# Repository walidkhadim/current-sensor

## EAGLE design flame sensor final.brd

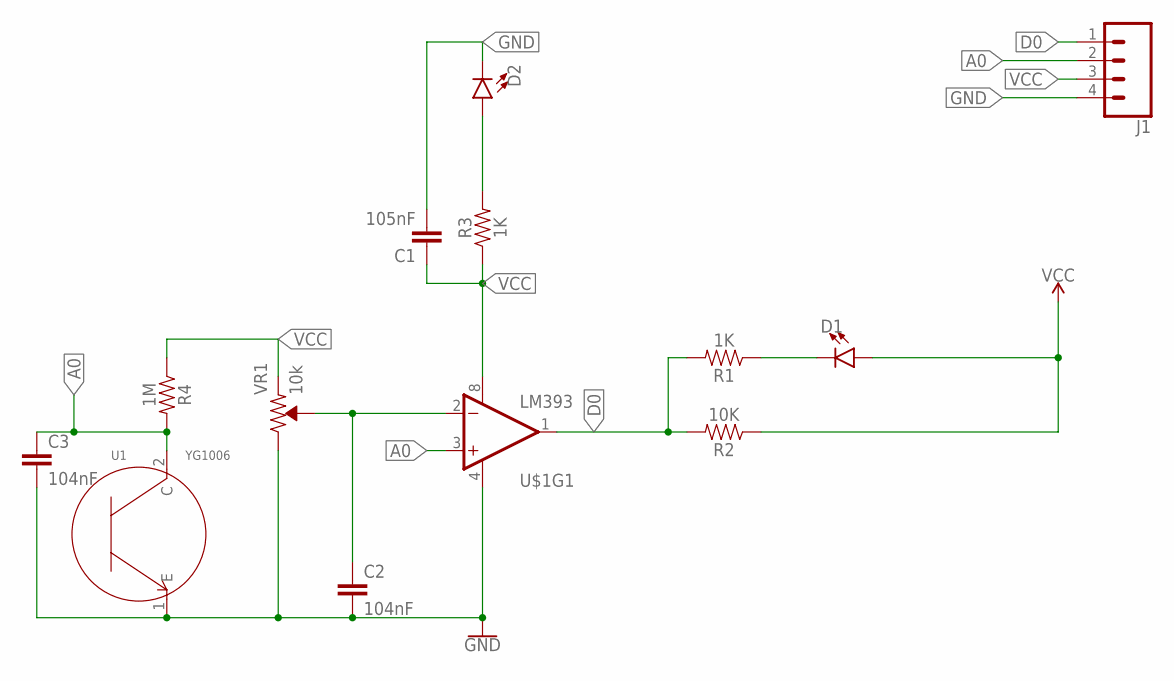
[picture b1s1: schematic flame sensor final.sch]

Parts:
C1: 105nF; 1206
C2, C3: 104nF; 1206
D1, D2: LED1206; LED-1206
J1: CONN_04; 1X04
R1, R3: 1K; 0603
R2: 10K; 0603
R4: 1M; 0603
U1: YG1006; 2P-2.54-5MM
U$1: LM393; SO08
VR1: 10k; TRIMPOT-SMD-5MM

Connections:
A0: C3.1, J1.2, R4.2, U1.2 (C), U$1.3 (+IN)
D0: J1.1, R1.2, R2.2, U$1.1 (OUT)
GND: C1.2, C2.2, C3.2, D2.C, J1.4, U1.1 (E), U$1.4 (V-), VR1.C (CW)
unnamed: D1.C, R1.1
unnamed: C2.1, U$1.2 (-IN), VR1.B (WIPER)
unnamed: D2.A, R3.2
VCC: C1.1, D1.A, J1.3, R2.1, R3.1, R4.1, U$1.8 (V+), VR1.A (CCW)

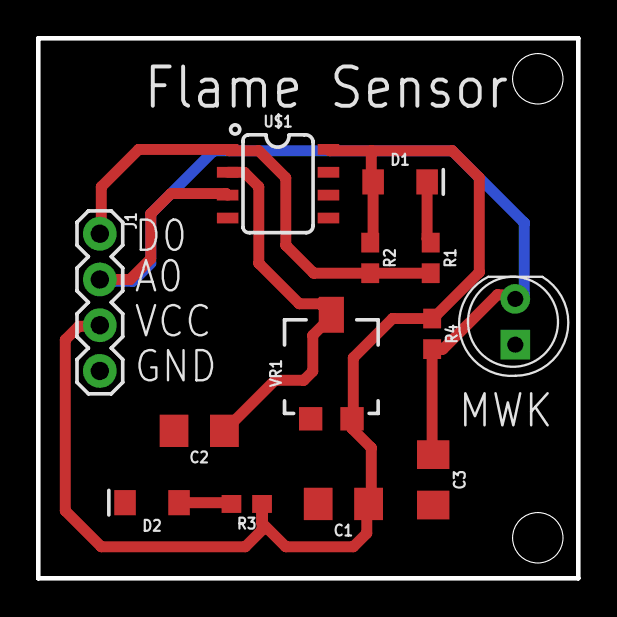
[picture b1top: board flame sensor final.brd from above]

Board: 2 copper layers, 30.0 x 30.0 mm, 13 parts (0 on the bottom side), 7 nets.

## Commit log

2017-08-05 PCB
    PCB
2017-08-05 SCHEMATIC
    SCHEMATIC

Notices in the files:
parts and their libraries:
SparkFun-Capacitors: Licensing: Creative Commons ShareAlike 4.0 International - https://creativecommons.org/licenses/by-sa/4.0
